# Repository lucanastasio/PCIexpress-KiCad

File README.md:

# PCIexpress-KiCad
PCI Express™ libraries and templates for KiCad
Made using guidelines from PCI Express™ Card Electromechanical Specification Rev. 1.2

Updated for KiCad 6

### Contents
**Templates:**
* x1 cards: full size, half length, low profile
* x4 cards: full size, half length, low profile
* x8 cards: full size, half length, low profile
* x16 cards: full size, half length, low profile

**Symbols:**
* x1
* x4
* x8
* x16
* Bracket

**Footprints:**
* x1 with multiple card outlines
* x4 with multiple card outlines
* x8 with multiple card outlines
* x16 with multiple card outlines
* Full height bracket (with 3D model)
* Low profile bracket (with 3D model)
* Low profile to full height adapter bracker (with 3D model)

### License
This documentation describes Open Hardware and is licensed under the CERN OHL v.1.2.

You may redistribute and modify this documentation under the terms of the CERN OHL v.1.2. (http://ohwr.org/cernohl). This documentation is distributed WITHOUT ANY EXPRESS OR IMPLIED WARRANTY, INCLUDING OF MERCHANTABILITY, SATISFACTORY QUALITY AND FITNESS FOR A PARTICULAR PURPOSE. Please see the CERN OHL v.1.2 for applicable conditions.

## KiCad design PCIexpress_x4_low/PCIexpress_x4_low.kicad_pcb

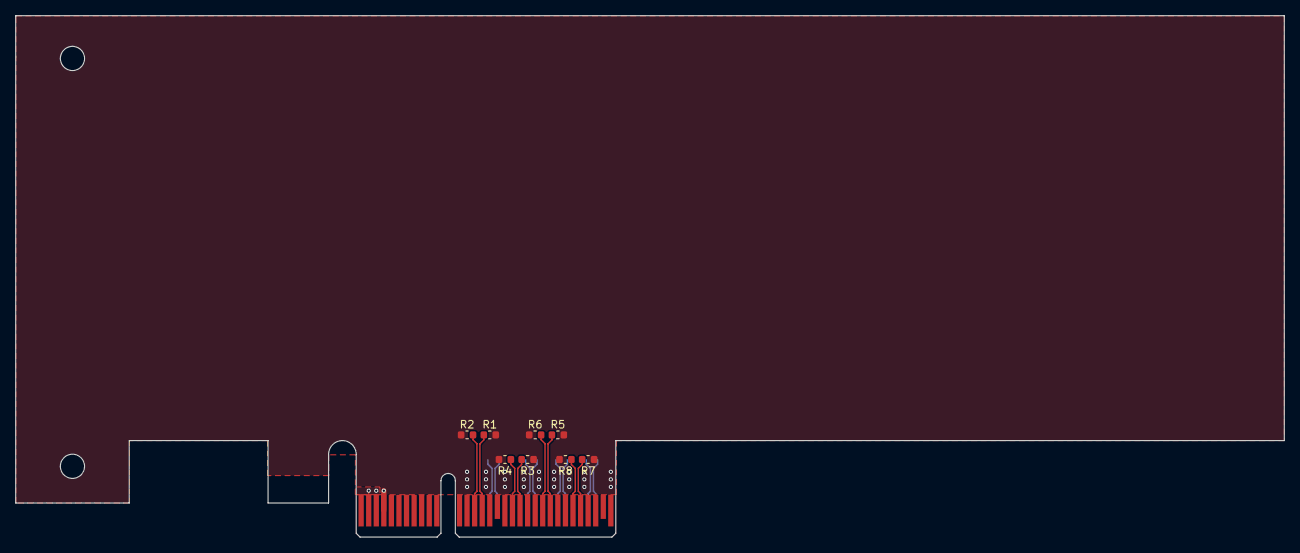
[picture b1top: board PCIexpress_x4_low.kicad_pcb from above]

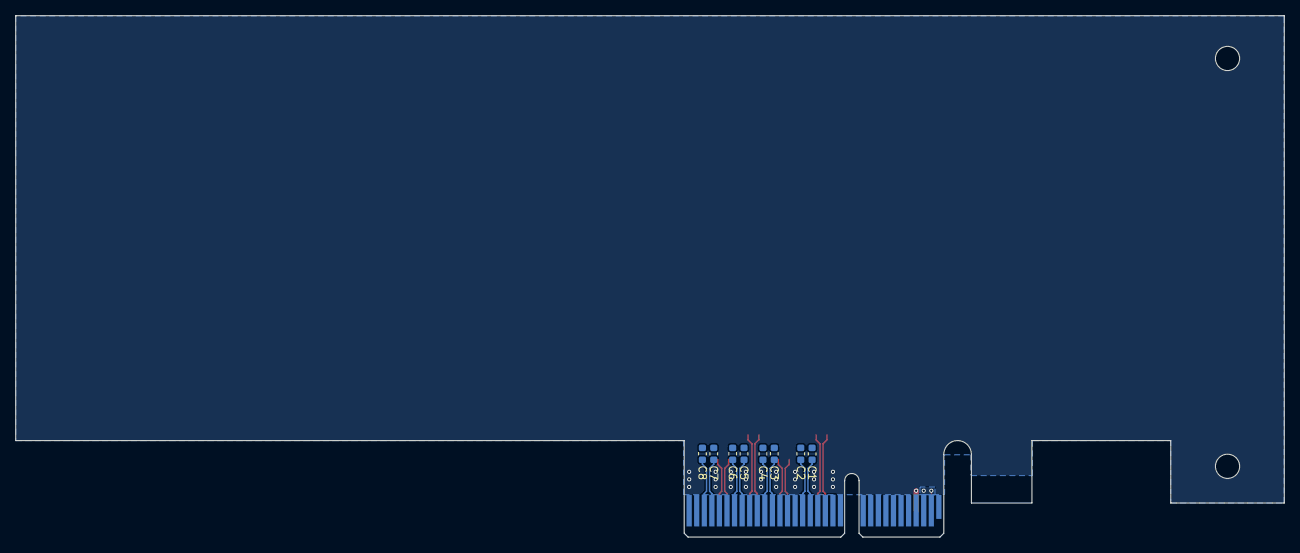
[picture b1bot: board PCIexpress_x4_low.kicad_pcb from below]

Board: 4 copper layers, 167.7 x 68.9 mm, 18 parts (8 on the bottom side), 19 nets.

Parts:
C1, C2, C3, C4, C5, C6, C7, C8: 100n; C_0603_1608Metric
J1: PCIexpress_bracket; PCIexpress_bracket_low
J2: PCIexpress_x4
R1, R2, R3, R4, R5, R6, R7, R8: 49.9; R_0603_1608Metric

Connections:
+3V3: J2.A9, J2.A10, J2.B8
+12V: J2.A2, J2.A3, J2.B1, J2.B2, J2.B3
/PCIexpress_connector/_PER0_N: C2.1, J2.A17
/PCIexpress_connector/_PER0_P: C1.2, J2.A16
/PCIexpress_connector/_PER1_N: C4.1, J2.A22
/PCIexpress_connector/_PER1_P: C3.2, J2.A21
/PCIexpress_connector/_PER2_N: C6.1, J2.A26
/PCIexpress_connector/_PER2_P: C5.2, J2.A25
/PCIexpress_connector/_PER3_N: C8.1, J2.A30
/PCIexpress_connector/_PER3_P: C7.2, J2.A29
/PET0_N: J2.B15, R1.1
/PET0_P: J2.B14, R2.1
/PET1_N: J2.B20, R3.1
/PET1_P: J2.B19, R4.1
/PET2_N: J2.B24, R5.1
/PET2_P: J2.B23, R6.1
/PET3_N: J2.B28, R7.1
/PET3_P: J2.B27, R8.1
GND: J2.A4, J2.A12, J2.A15, J2.A18, J2.A20, J2.A23, J2.A24, J2.A27, J2.A28, J2.A31, J2.B4, J2.B7, J2.B13, J2.B16, J2.B18, J2.B21, J2.B22, J2.B25, J2.B26, J2.B29, J2.B32, R1.2, R2.2, R3.2, R4.2, R5.2, R6.2, R7.2, R8.2

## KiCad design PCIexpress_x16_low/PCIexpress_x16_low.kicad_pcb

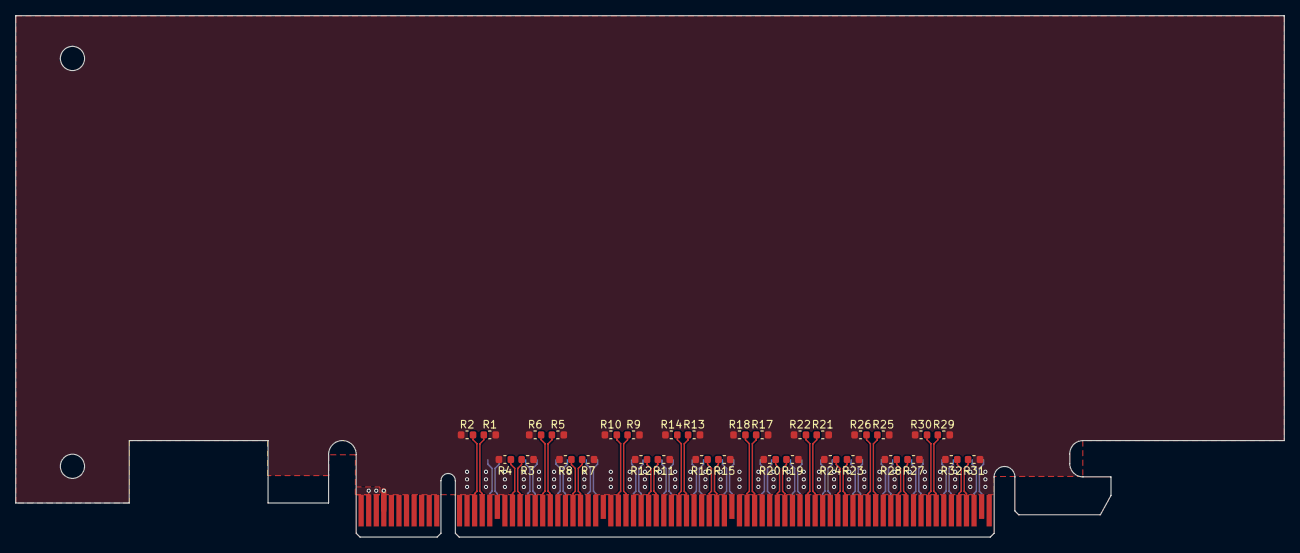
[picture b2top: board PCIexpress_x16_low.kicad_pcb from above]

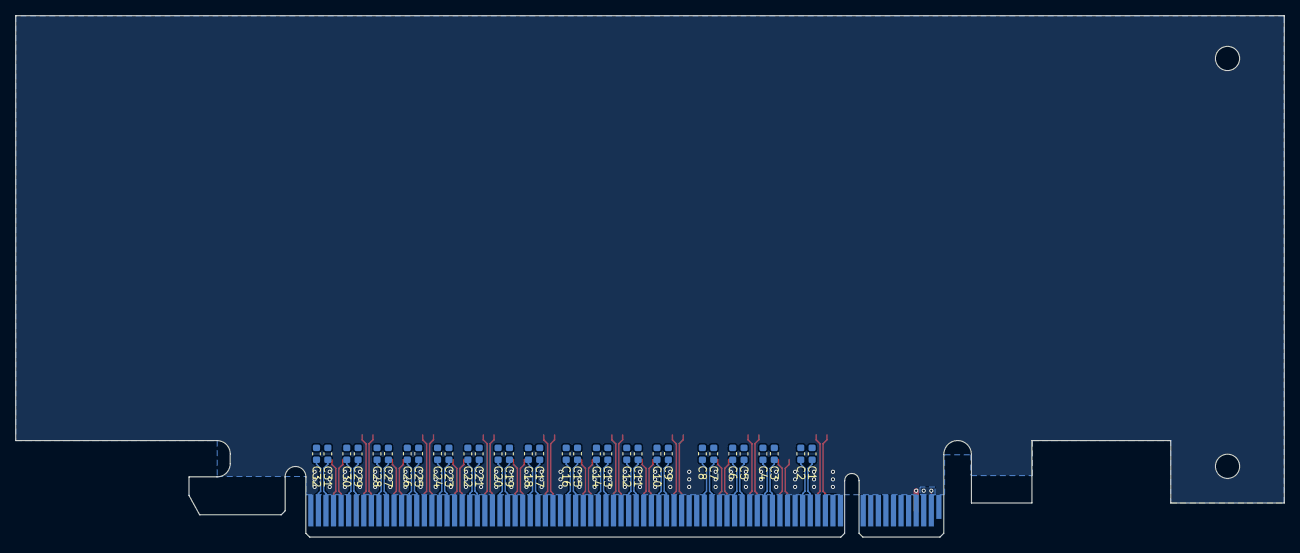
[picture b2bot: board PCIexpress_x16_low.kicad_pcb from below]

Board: 4 copper layers, 167.7 x 68.9 mm, 66 parts (32 on the bottom side), 67 nets.

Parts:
C1, C2, C3, C4, C5, C6, C7, C8, C9, C10, C11, C12, C13, C14, C15, C16, C17, C18, C19, C20, C21, C22, C23, C24, C25, C26, C27, C28, C29, C30, C31, C32: 100n; C_0603_1608Metric
J1: PCIexpress_bracket; PCIexpress_bracket_low
J2: PCIexpress_x16
R1, R2, R3, R4, R5, R6, R7, R8, R9, R10, R11, R12, R13, R14, R15, R16, R17, R18, R19, R20, R21, R22, R23, R24, R25, R26, R27, R28, R29, R30, R31, R32: 49.9; R_0603_1608Metric

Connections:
+3V3: J2.A9, J2.A10, J2.B8
+12V: J2.A2, J2.A3, J2.B1, J2.B2, J2.B3
/PCIexpress_connector/_PER0_N: C2.1, J2.A17
/PCIexpress_connector/_PER0_P: C1.2, J2.A16
/PCIexpress_connector/_PER1_N: C4.1, J2.A22
/PCIexpress_connector/_PER1_P: C3.2, J2.A21
/PCIexpress_connector/_PER2_N: C6.1, J2.A26
/PCIexpress_connector/_PER2_P: C5.2, J2.A25
/PCIexpress_connector/_PER3_N: C8.1, J2.A30
/PCIexpress_connector/_PER3_P: C7.2, J2.A29
/PCIexpress_connector/_PER4_N: C10.1, J2.A36
/PCIexpress_connector/_PER4_P: C9.2, J2.A35
/PCIexpress_connector/_PER5_N: C12.1, J2.A40
/PCIexpress_connector/_PER5_P: C11.2, J2.A39
/PCIexpress_connector/_PER6_N: C14.1, J2.A44
/PCIexpress_connector/_PER6_P: C13.2, J2.A43
/PCIexpress_connector/_PER7_N: C16.1, J2.A48
/PCIexpress_connector/_PER7_P: C15.2, J2.A47
/PCIexpress_connector/_PER8_N: C18.1, J2.A53
/PCIexpress_connector/_PER8_P: C17.2, J2.A52
/PCIexpress_connector/_PER9_N: C20.1, J2.A57
/PCIexpress_connector/_PER9_P: C19.2, J2.A56
/PCIexpress_connector/_PER10_N: C22.1, J2.A61
/PCIexpress_connector/_PER10_P: C21.2, J2.A60
/PCIexpress_connector/_PER11_N: C24.1, J2.A65
/PCIexpress_connector/_PER11_P: C23.2, J2.A64
/PCIexpress_connector/_PER12_N: C26.1, J2.A69
/PCIexpress_connector/_PER12_P: C25.2, J2.A68
/PCIexpress_connector/_PER13_N: C28.1, J2.A73
/PCIexpress_connector/_PER13_P: C27.2, J2.A72
/PCIexpress_connector/_PER14_N: C30.1, J2.A77
/PCIexpress_connector/_PER14_P: C29.2, J2.A76
/PCIexpress_connector/_PER15_N: C32.1, J2.A81
/PCIexpress_connector/_PER15_P: C31.2, J2.A80
/PET0_N: J2.B15, R1.1
/PET0_P: J2.B14, R2.1
/PET1_N: J2.B20, R3.1
/PET1_P: J2.B19, R4.1
/PET2_N: J2.B24, R5.1
/PET2_P: J2.B23, R6.1
/PET3_N: J2.B28, R7.1
/PET3_P: J2.B27, R8.1
/PET4_N: J2.B34, R9.1
/PET4_P: J2.B33, R10.1
/PET5_N: J2.B38, R11.1
/PET5_P: J2.B37, R12.1
/PET6_N: J2.B42, R13.1
/PET6_P: J2.B41, R14.1
/PET7_N: J2.B46, R15.1
/PET7_P: J2.B45, R16.1
/PET8_N: J2.B51, R17.1
/PET8_P: J2.B50, R18.1
/PET9_N: J2.B55, R19.1
/PET9_P: J2.B54, R20.1
/PET10_N: J2.B59, R21.1
/PET10_P: J2.B58, R22.1
/PET11_N: J2.B63, R23.1
/PET11_P: J2.B62, R24.1
/PET12_N: J2.B67, R25.1
/PET12_P: J2.B66, R26.1
/PET13_N: J2.B71, R27.1
/PET13_P: J2.B70, R28.1
/PET14_N: J2.B75, R29.1
/PET14_P: J2.B74, R30.1
/PET15_N: J2.B79, R31.1
/PET15_P: J2.B78, R32.1
GND: J2.A4, J2.A12, J2.A15, J2.A18, J2.A20, J2.A23, J2.A24, J2.A27, J2.A28, J2.A31, J2.A34, J2.A37, J2.A38, J2.A41, J2.A42, J2.A45, J2.A46, J2.A49, J2.A51, J2.A54, J2.A55, J2.A58, J2.A59, J2.A62, J2.A63, J2.A66, J2.A67, J2.A70, J2.A71, J2.A74, J2.A75, J2.A78, J2.A79, J2.A82, J2.B4, J2.B7, J2.B13, J2.B16, J2.B18, J2.B21, J2.B22, J2.B25, J2.B26, J2.B29, J2.B32, J2.B35, J2.B36, J2.B39, J2.B40, J2.B43, J2.B44, J2.B47, J2.B49, J2.B52, J2.B53, J2.B56, J2.B57, J2.B60, J2.B61, J2.B64, J2.B65, J2.B68, J2.B69, J2.B72, J2.B73, J2.B76, J2.B77, J2.B80, R1.2, R2.2, R3.2, R4.2, R5.2, R6.2, R7.2, R8.2, R9.2, R10.2, R11.2, R12.2, R13.2, R14.2, R15.2, R16.2, R17.2, R18.2, R19.2, R20.2, R21.2, R22.2, R23.2, R24.2, R25.2, R26.2, R27.2, R28.2, R29.2, R30.2, R31.2, R32.2

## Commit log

2019-07-20 first
2019-07-26 half x16
2019-08-11 templates
2019-11-28 release
2023-02-02 KiCad 6 update
2024-01-14 added meta folder and very basic html
    just enough to make it work in kacad templates
2024-01-14 added meta folder and very basic html
    just enough tomake it work as kicad template
